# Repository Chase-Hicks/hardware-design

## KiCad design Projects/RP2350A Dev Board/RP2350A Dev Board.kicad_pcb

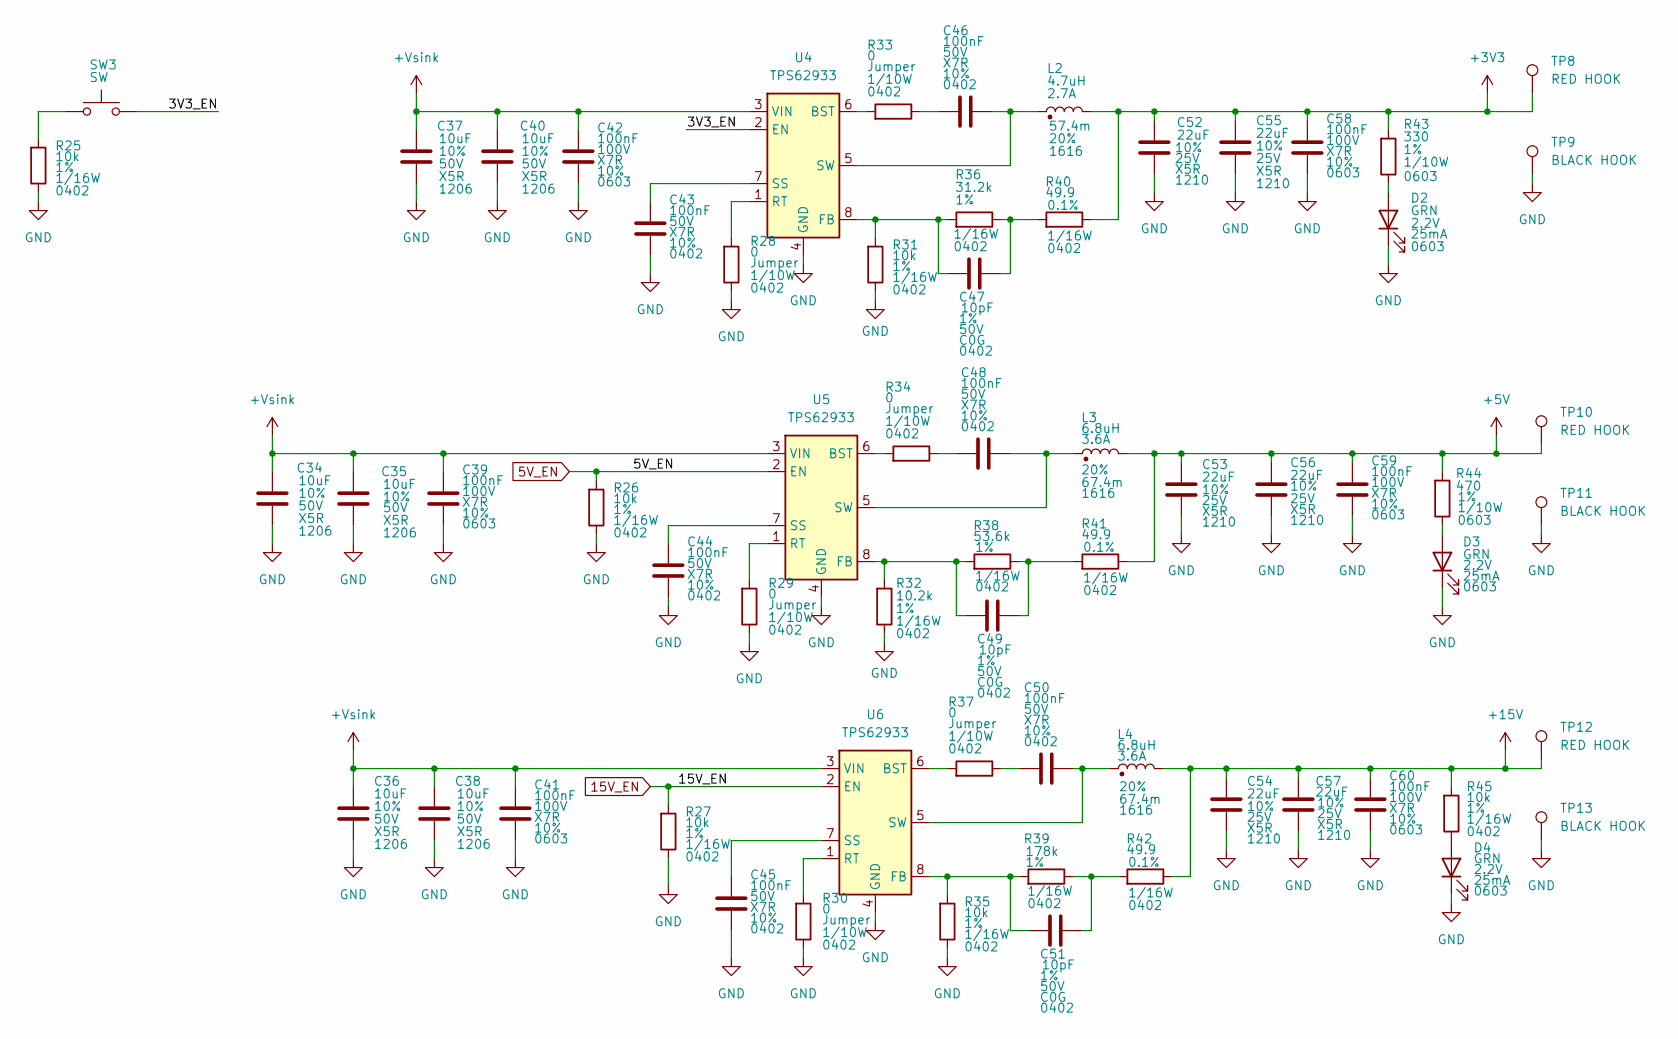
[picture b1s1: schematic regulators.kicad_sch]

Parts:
C34, C35, C36, C37, C38, C40: 10uF; C_1206_3216Metric_2; Voltage 50V; Tolerance 10%; Part Description CAP, 10uF, 25V, X5R, 10%, 1206
C39, C41, C42, C58, C59, C60: 100nF; C_0603_1608Metric_2; Voltage 100V; Tolerance 10%; Part Description CAP, 100nF, 100V, X7R, 10%, 0603
C43, C44, C45, C46, C48, C50: 100nF; C_0402_1005Metric_2; Voltage 50V; Tolerance 10%; Part Description CAP, 100nF, 50V, X7R, 10%, 0402
C47, C49, C51: 10pF; C_0402_1005Metric_2; Voltage 50V; Tolerance 1%; Part Description CAP, 10pF, 50V, C0G, 1%, 0402
C52, C53, C54, C55, C56, C57: 22uF; C_1210_3225Metric_2; Voltage 25V; Tolerance 10%; Part Description CAP, 22uF, 25V, X5R, 10%, 1210
D2, D3, D4: GRN; LED_0603_1608Metric_2; Voltage 2.2V; Part Description LED, GRN, 2.2V, 0603
L2: 4.7uH; XAL-4030-xxx; Tolerance 20%; Part Description IND, 4.7uH, 4.6A, 40.1m, 20%, 1616
L3, L4: 6.8uH; XEL-4030-xxx; Tolerance 20%; Part Description IND, 6.8uH, 3.6A, 67.4m, 20%, 1616
R25, R26, R27, R31, R35, R45: 10k; R_0402_1005Metric_2; Tolerance 1%; Part Description RESIST, 10k, 1/16W, 1%, 0402
R28, R29, R30, R33, R34, R37: 0; R_0402_1005Metric_2; Tolerance Jumper; Part Description RESIST, 0, 1/10W, 0402
R32: 10.2k; R_0402_1005Metric_2; Tolerance 1%; Part Description RESIST, 10.2k, 1/16W, 1%, 0402
R36: 31.2k; R_0402_1005Metric_2; Tolerance 1%; Part Description RESIST, 31.2k, 1/16W, 0.1%, 0402
R38: 53.6k; R_0402_1005Metric_2; Tolerance 1%; Part Description RESIST, 53.6k, 1/16W, 1%, 0402
R39: 178k; R_0402_1005Metric_2; Tolerance 1%; Part Description RESIST, 178k, 1/16W, 1%, 0402
R40, R41, R42: 49.9; R_0402_1005Metric_2; Tolerance 0.1%; Part Description RESIST, 49.9, 1/16W, 0.1%, 0403
R43: 330; R_0603_1608Metric_2; Tolerance 1%; Part Description RESIST, 330, 1/10W, 1%, 0603
R44: 470; R_0603_1608Metric_2; Tolerance 1%; Part Description RESIST, 470, 1/10W, 1%, 0603
SW3: SW; PTS815; Part Description SW, SMD, 4P
TP8, TP10, TP12: RED HOOK; KEYSTONE_519xTR; MFG PN 5190TR
TP9, TP11, TP13: BLACK HOOK; KEYSTONE_519xTR; MFG PN 5191TR
U4, U5, U6: TPS62933; SOT-583-8; Part Description IC, SMD, REG, BUCK, STEP-DOWN, 30VIN, 3A

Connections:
5V_EN: R26.1, U5.2 (EN); also elsewhere on the board
15V_EN: R27.1, U6.2 (EN); also elsewhere on the board
+3V3: C52.1, C55.1, C58.1, L2.2, R40.2, R43.1, TP8.1 (1_1); also elsewhere on the board
+5V: C53.1, C56.1, C59.1, L3.2, R41.2, R44.1, TP10.1 (1_1); also elsewhere on the board
+15V: C54.1, C57.1, C60.1, L4.2, R42.2, R45.1, TP12.1 (1_1); also elsewhere on the board
+Vsink: C34.1, C35.1, C36.1, C37.1, C38.1, C39.1, C40.1, C41.1, C42.1, U4.3 (VIN), U5.3 (VIN), U6.3 (VIN); also elsewhere on the board
/Regulators/3V3_EN: SW3.4, U4.2 (EN)
GND: C34.2, C35.2, C36.2, C37.2, C38.2, C39.2, C40.2, C41.2, C42.2, C43.2, C44.2, C45.2, C52.2, C53.2, C54.2, C55.2, C56.2, C57.2, C58.2, C59.2, C60.2, D2.1 (K), D3.1 (K), D4.1 (K), R25.2, R26.2, R27.2, R28.2, R29.2, R30.2, R31.2, R32.2, R35.2, TP9.1 (1_1), TP11.1 (1_1), TP13.1 (1_1), U4.4 (GND), U5.4 (GND), U6.4 (GND); also elsewhere on the board
unnamed: C46.1, R33.2
unnamed: C47.1, R36.2, R40.1
unnamed: C48.1, R34.2
unnamed: C49.1, R38.2, R41.1
unnamed: C50.1, R37.2
unnamed: C51.1, R39.2, R42.1
unnamed: D2.2 (A), R43.2
unnamed: D3.2 (A), R44.2
unnamed: D4.2 (A), R45.2
unnamed: R25.1, SW3.1
unnamed: R33.1, U4.6 (BST)
unnamed: C47.2, R31.1, R36.1, U4.8 (FB)
unnamed: R28.1, U4.1 (RT)
unnamed: C43.1, U4.7 (SS)
unnamed: C46.2, L2.1, U4.5 (SW)
unnamed: R34.1, U5.6 (BST)
unnamed: C49.2, R32.1, R38.1, U5.8 (FB)
unnamed: R29.1, U5.1 (RT)
unnamed: C44.1, U5.7 (SS)
unnamed: C48.2, L3.1, U5.5 (SW)
unnamed: R37.1, U6.6 (BST)
unnamed: C51.2, R35.1, R39.1, U6.8 (FB)
unnamed: R30.1, U6.1 (RT)
unnamed: C45.1, U6.7 (SS)
unnamed: C50.2, L4.1, U6.5 (SW)

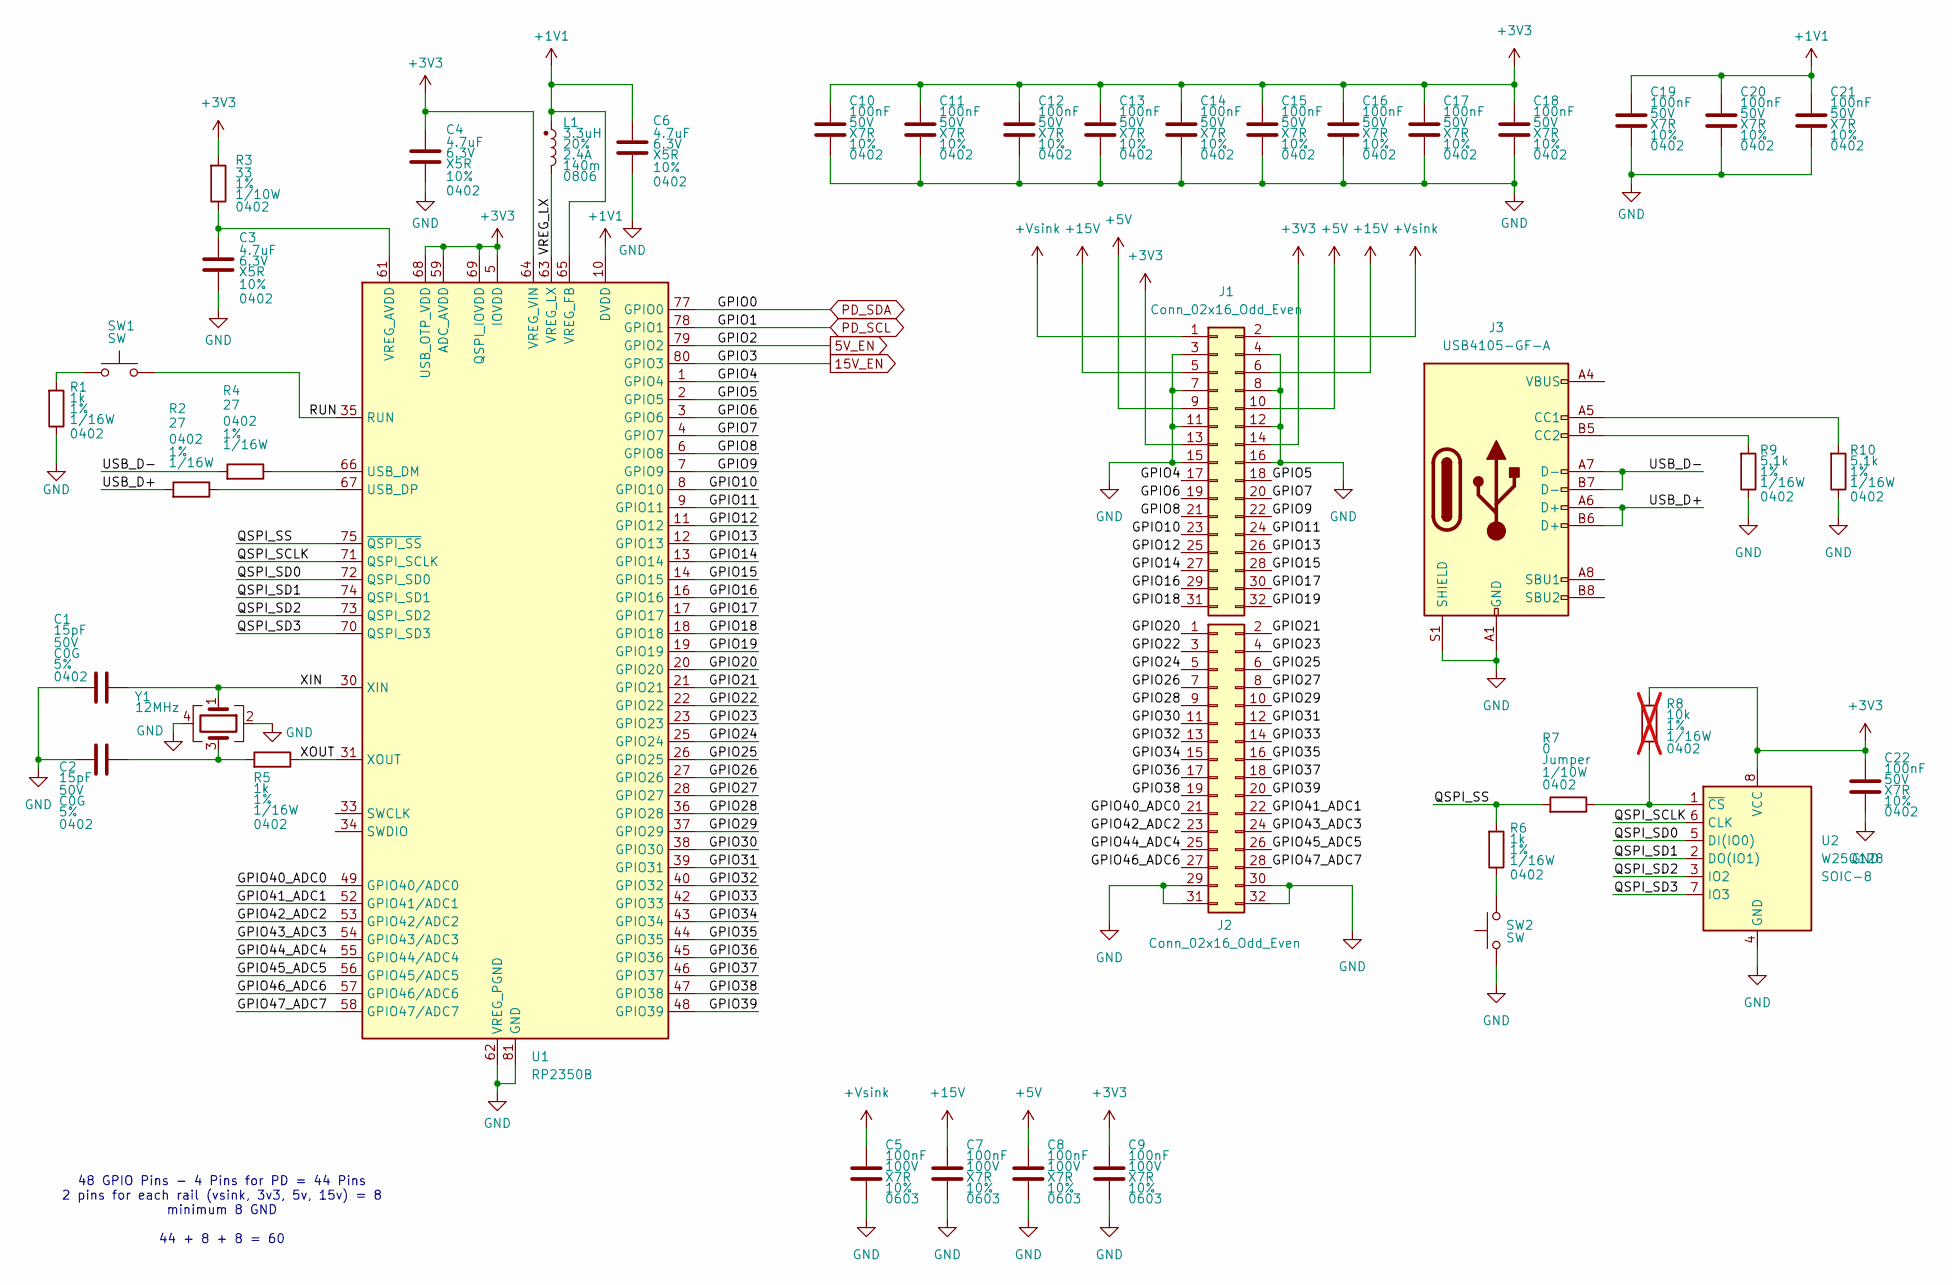
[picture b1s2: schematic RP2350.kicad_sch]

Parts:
C1, C2: 15pF; C_0402_1005Metric_2; Voltage 50V; Tolerance 5%; Part Description CAP, 15pF, 50V, C0G, 5%, 0402
C3: 4.7uF; C_0402_1005Metric_2; Voltage 6.3V; Tolerance 10%; Part Description CAP, 4.7uF, 6.3V, X5R, 10%, 0402
C4, C6: 4.7uF; C_0402_1005Metric_small_pads; Voltage 6.3V; Tolerance 10%; Part Description CAP, 4.7uF, 6.3V, X5R, 10%, 0402
C5, C7, C8, C9: 100nF; C_0603_1608Metric_2; Voltage 100V; Tolerance 10%; Part Description CAP, 100nF, 100V, X7R, 10%, 0603
C10, C11, C12, C13, C14, C15, C16, C17, C18, C19, C20, C21, C22: 100nF; C_0402_1005Metric_2; Voltage 50V; Tolerance 10%; Part Description CAP, 100nF, 50V, X7R, 10%, 0402
J1, J2: Conn_02x16_Odd_Even; PinSocket_2x16_P2.54mm_Vertical
J3: USB4105-GF-A; USB_C_Receptacle_GCT_USB4105-xx-A_16P_TopMnt_Horizontal; Part Description CONN, USB C, 2.0, 16P
L1: 3.3uH; L_pol_2016; Tolerance 20%; Part Description IND, 3.3uH, 2.4A, 140m, 20%, 0806
R1, R5, R6: 1k; R_0402_1005Metric_2; Tolerance 1%; Part Description RESIST, 1k, 1/16W, 1%, 0402
R2, R4: 27; R_0402_1005Metric_2; Tolerance 1%; Part Description RESIST, 27, 1/16W, 1%, 0402
R3: 33; R_0402_1005Metric_2; Tolerance 1%; Part Description RESIST, 33, 1/10W, 1%, 0402
R7: 0; R_0402_1005Metric_2; Tolerance Jumper; Part Description RESIST, 0, 1/10W, 0402
R8: 10k; R_0402_1005Metric_2; Tolerance 1%; Part Description RESIST, 10k, 1/16W, 1%, 0402; not fitted
R9, R10: 5.1k; R_0402_1005Metric_2; Tolerance 1%; Part Description RESIST, 5.1k, 1/16W, 1%, 0402
SW1, SW2: SW; PTS815; Part Description SW, SMD, 4P
U1: RP2350B; QFN-80-1EP_10x10mm_P0.4mm_EP3.4x3.4mm; Part Description IC, MCU, RP2350B, QFN
U2: W25Q128; SOIC-8_5.3x5.3mm_P1.27mm; Part Description IC, QSPI, 128Mb, Flash, SOIC
Y1: 12MHz; Crystal_SMD_Abracon_ABM8G-4Pin_3.2x2.5mm; Part Description CRYSTAL, 12Mhz, 30ppm, 10pF, 4-SMD

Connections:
5V_EN: U1.79 (GPIO2); also elsewhere on the board
15V_EN: U1.80 (GPIO3); also elsewhere on the board
+1V1: C6.1, C19.1, C20.1, C21.1, L1.1, U1.10 (DVDD), U1.32 (DVDD), U1.51 (DVDD), U1.65 (VREG_FB)
+3V3: C4.1, C9.1, C10.1, C11.1, C12.1, C13.1, C14.1, C15.1, C16.1, C17.1, C18.1, C22.1, J1.13, J1.14, R3.1, R8.1, U1.5 (IOVDD), U1.15 (IOVDD), U1.24 (IOVDD), U1.29 (IOVDD), U1.41 (IOVDD), U1.50 (IOVDD), U1.59 (ADC_AVDD), U1.60 (IOVDD), U1.64 (VREG_VIN), U1.68 (USB_OTP_VDD), U1.69 (QSPI_IOVDD), U1.76 (IOVDD), U2.8 (VCC); also elsewhere on the board
+5V: C8.1, J1.9, J1.10; also elsewhere on the board
+15V: C7.1, J1.5, J1.6; also elsewhere on the board
+Vsink: C5.1, J1.1, J1.2; also elsewhere on the board
/RP2350/GPIO4: J1.17, U1.1 (GPIO4)
/RP2350/GPIO5: J1.18, U1.2 (GPIO5)
/RP2350/GPIO6: J1.19, U1.3 (GPIO6)
/RP2350/GPIO7: J1.20, U1.4 (GPIO7)
/RP2350/GPIO8: J1.21, U1.6 (GPIO8)
/RP2350/GPIO9: J1.22, U1.7 (GPIO9)
/RP2350/GPIO10: J1.23, U1.8 (GPIO10)
/RP2350/GPIO11: J1.24, U1.9 (GPIO11)
/RP2350/GPIO12: J1.25, U1.11 (GPIO12)
/RP2350/GPIO13: J1.26, U1.12 (GPIO13)
/RP2350/GPIO14: J1.27, U1.13 (GPIO14)
/RP2350/GPIO15: J1.28, U1.14 (GPIO15)
/RP2350/GPIO16: J1.29, U1.16 (GPIO16)
/RP2350/GPIO17: J1.30, U1.17 (GPIO17)
/RP2350/GPIO18: J1.31, U1.18 (GPIO18)
/RP2350/GPIO19: J1.32, U1.19 (GPIO19)
/RP2350/GPIO20: J2.1, U1.20 (GPIO20)
/RP2350/GPIO21: J2.2, U1.21 (GPIO21)
/RP2350/GPIO22: J2.3, U1.22 (GPIO22)
/RP2350/GPIO23: J2.4, U1.23 (GPIO23)
/RP2350/GPIO24: J2.5, U1.25 (GPIO24)
/RP2350/GPIO25: J2.6, U1.26 (GPIO25)
/RP2350/GPIO26: J2.7, U1.27 (GPIO26)
/RP2350/GPIO27: J2.8, U1.28 (GPIO27)
/RP2350/GPIO28: J2.9, U1.36 (GPIO28)
/RP2350/GPIO29: J2.10, U1.37 (GPIO29)
/RP2350/GPIO30: J2.11, U1.38 (GPIO30)
/RP2350/GPIO31: J2.12, U1.39 (GPIO31)
/RP2350/GPIO32: J2.13, U1.40 (GPIO32)
/RP2350/GPIO33: J2.14, U1.42 (GPIO33)
/RP2350/GPIO34: J2.15, U1.43 (GPIO34)
/RP2350/GPIO35: J2.16, U1.44 (GPIO35)
/RP2350/GPIO36: J2.17, U1.45 (GPIO36)
/RP2350/GPIO37: J2.18, U1.46 (GPIO37)
/RP2350/GPIO38: J2.19, U1.47 (GPIO38)
/RP2350/GPIO39: J2.20, U1.48 (GPIO39)
/RP2350/GPIO40_ADC0: J2.21, U1.49 (GPIO40/ADC0)
/RP2350/GPIO41_ADC1: J2.22, U1.52 (GPIO41/ADC1)
/RP2350/GPIO42_ADC2: J2.23, U1.53 (GPIO42/ADC2)
/RP2350/GPIO43_ADC3: J2.24, U1.54 (GPIO43/ADC3)
/RP2350/GPIO44_ADC4: J2.25, U1.55 (GPIO44/ADC4)
/RP2350/GPIO45_ADC5: J2.26, U1.56 (GPIO45/ADC5)
/RP2350/GPIO46_ADC6: J2.27, U1.57 (GPIO46/ADC6)
/RP2350/GPIO47_ADC7: J2.28, U1.58 (GPIO47/ADC7)
/RP2350/QSPI_SCLK: U1.71 (QSPI_SCLK), U2.6 (CLK)
/RP2350/QSPI_SD0: U1.72 (QSPI_SD0), U2.5 (DI(IO0))
/RP2350/QSPI_SD1: U1.74 (QSPI_SD1), U2.2 (DO(IO1))
/RP2350/QSPI_SD2: U1.73 (QSPI_SD2), U2.3 (IO2)
/RP2350/QSPI_SD3: U1.70 (QSPI_SD3), U2.7 (IO3)
/RP2350/QSPI_SS: R6.1, R7.1, U1.75 (~QSPI_SS)
/RP2350/RUN: SW1.4, U1.35 (RUN)
/RP2350/USB_D+: J3.A6 (D+), J3.B6 (D+), R2.1
/RP2350/USB_D-: J3.A7 (D-), J3.B7 (D-), R4.1
/RP2350/VREG_LX: L1.2, U1.63 (VREG_LX)
/RP2350/XIN: C1.2, U1.30 (XIN), Y1.1
/RP2350/XOUT: R5.2, U1.31 (XOUT)
GND: C1.1, C2.1, C3.2, C4.2, C5.2, C6.2, C7.2, C8.2, C9.2, C10.2, C11.2, C12.2, C13.2, C14.2, C15.2, C16.2, C17.2, C18.2, C19.2, C20.2, C21.2, C22.2, J1.3, J1.4, J1.7, J1.8, J1.11, J1.12, J1.15, J1.16, J2.29, J2.30, J2.31, J2.32, J3.A1 (GND), J3.A12 (GND), J3.B1 (GND), J3.B12 (GND), J3.S1 (SHIELD), R1.2, R9.2, R10.2, SW2.1, U1.62 (VREG_PGND), U1.81 (GND), U2.4 (GND), Y1.2, Y1.4; also elsewhere on the board
unnamed: C2.2, R5.1, Y1.3
unnamed: J3.A5 (CC1), R10.1
unnamed: J3.B5 (CC2), R9.1
unnamed: J3.A4 (VBUS), J3.A9 (VBUS), J3.B4 (VBUS), J3.B9 (VBUS)
unnamed: R1.1, SW1.1
unnamed: R6.2, SW2.4
unnamed: R4.2, U1.66 (USB_DM)
unnamed: R2.2, U1.67 (USB_DP)
unnamed: C3.1, R3.2, U1.61 (VREG_AVDD)
unnamed: R7.2, R8.2, U2.1 (~CS)
PD_SCL: U1.78 (GPIO1); also elsewhere on the board
PD_SDA: U1.77 (GPIO0); also elsewhere on the board

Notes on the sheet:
48 GPIO Pins - 4 Pins for PD = 44 Pins 2 pins for each rail (vsink, 3v3, 5v, 15v) = 8 minimum 8 GND 44 + 8 + 8 = 60

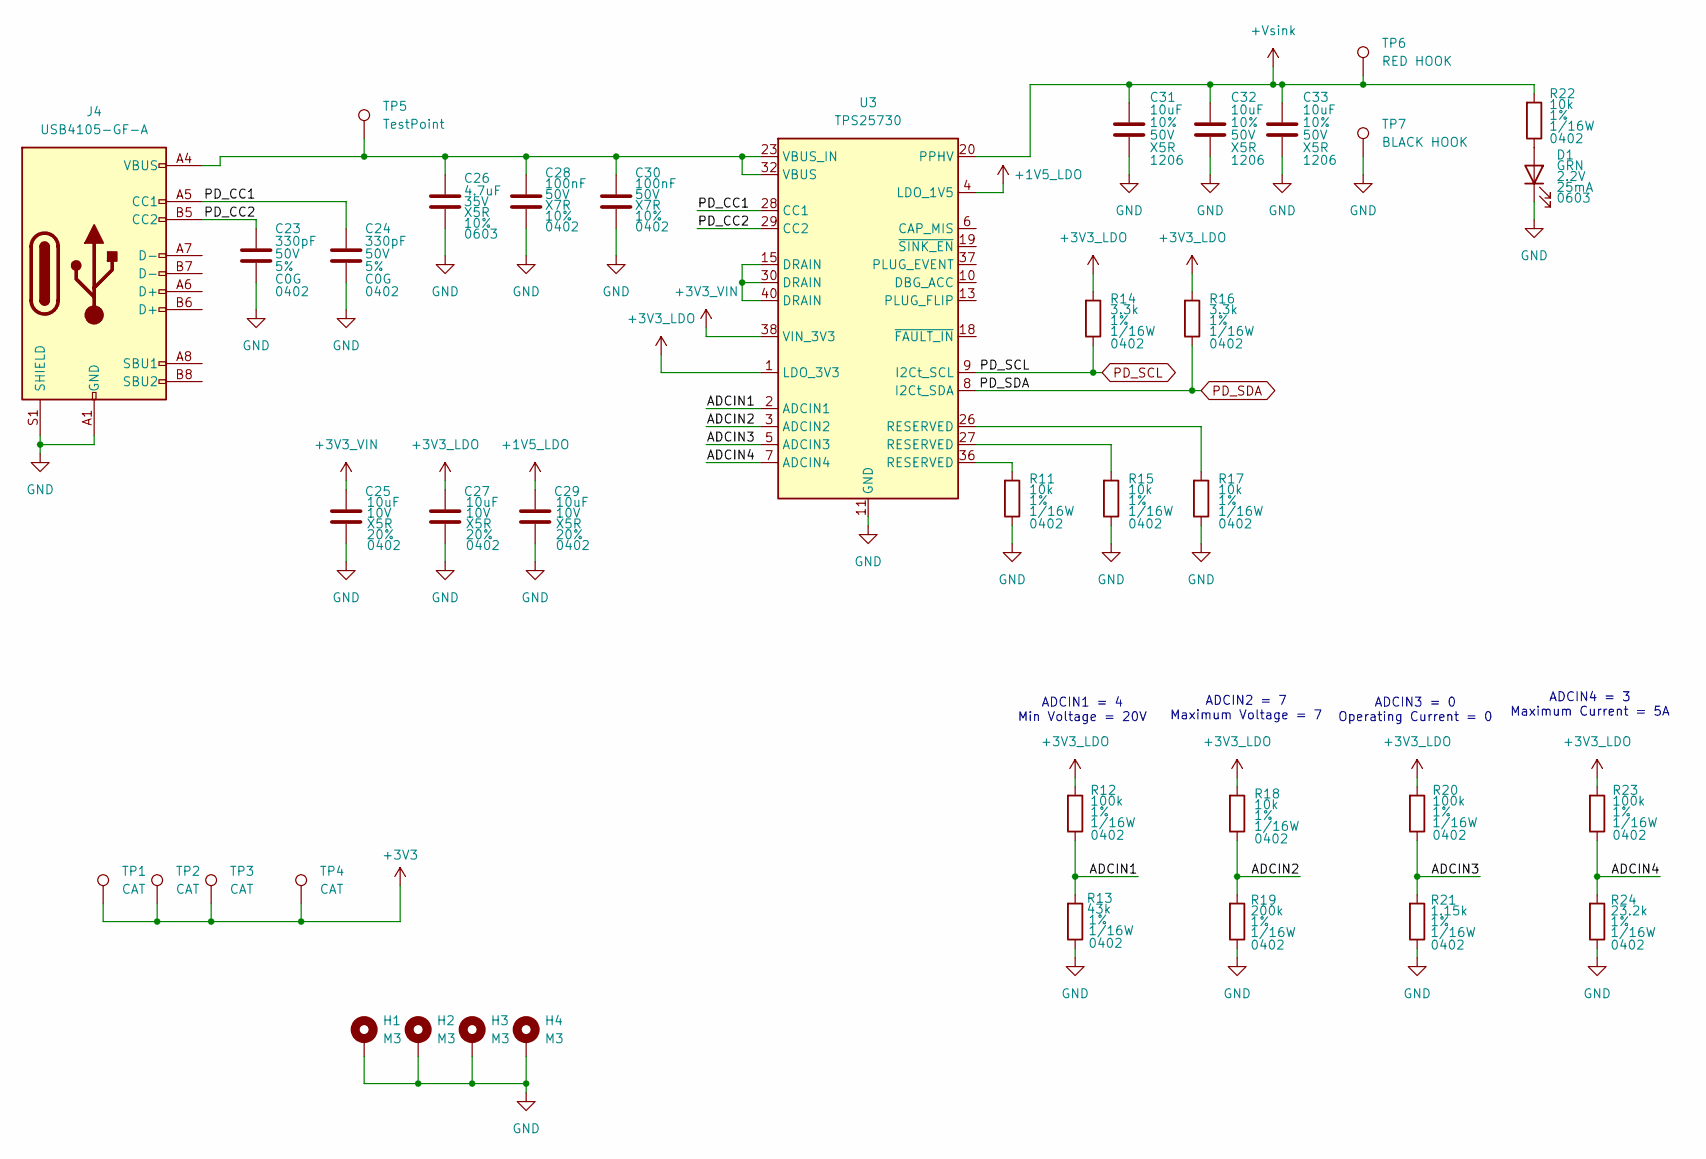
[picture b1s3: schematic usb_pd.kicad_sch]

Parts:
C23, C24: 330pF; C_0402_1005Metric_2; Voltage 50V; Tolerance 5%; Part Description CAP, 330pF, 50V, C0G, 5%, 0402
C25, C27, C29: 10uF; C_0402_1005Metric_2; Voltage 10V; Tolerance 20%; Part Description CAP, 10uF, 10V, X5R, 20%, 0402
C26: 4.7uF; C_0603_1608Metric_2; Voltage 35V; Tolerance 10%; Part Description CAP, 4.7uF, 35V, X5R, 10%, 0603
C28, C30: 100nF; C_0402_1005Metric_2; Voltage 50V; Tolerance 10%; Part Description CAP, 100nF, 50V, X7R, 10%, 0402
C31, C32, C33: 10uF; C_1206_3216Metric_2; Voltage 50V; Tolerance 10%; Part Description CAP, 10uF, 25V, X5R, 10%, 1206
D1: GRN; LED_0603_1608Metric_2; Voltage 2.2V; Part Description LED, GRN, 2.2V, 0603
H1, H2, H3, H4: M3; MountingHole_3.2mm_M3_Pad_Via; MFG PN N/A
J4: USB4105-GF-A; USB_C_Receptacle_GCT_USB4105-xx-A_16P_TopMnt_Horizontal; Part Description CONN, USB C, 2.0, 16P
R11, R15, R17, R18, R22: 10k; R_0402_1005Metric_2; Tolerance 1%; Part Description RESIST, 10k, 1/16W, 1%, 0402
R12, R20, R23: 100k; R_0402_1005Metric_2; Tolerance 1%; Part Description RESIST, 100k, 1/16W, 1%, 0402
R13: 43k; R_0402_1005Metric_2; Tolerance 1%; Part Description RESIST, 43k, 1/16W, 1%, 0402
R14, R16: 3.3k; R_0402_1005Metric_2; Tolerance 1%; Part Description RESIST, 3.3k, 1/16W, 1%, 0402
R19: 200k; R_0402_1005Metric_2; Tolerance 1%; Part Description RESIST, 200k, 1/16W, 1%, 0402
R21: 1.15k; R_0402_1005Metric_2; Tolerance 1%; Part Description RESIST, 1.15k, 1/16W, 1%, 0402
R24: 23.2k; R_0402_1005Metric_2; Tolerance 1%; Part Description RESIST, 23.2k, 1/16W, 1%, 0402
TP1: CAT; Cat_4
TP2: CAT; Cat_3
TP3: CAT; Cat_2
TP4: CAT; Cat
TP5: TestPoint; TestPoint_Pad_D1.0mm
TP6: RED HOOK; KEYSTONE_519xTR; MFG PN 5190TR
TP7: BLACK HOOK; KEYSTONE_519xTR; MFG PN 5191TR
U3: TPS25730; Texas_REF0038A_WQFN-38-2EP_6x4mm_P0.4; Part Description IC, USB PD, FET, WQFN-38

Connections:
+1V5_LDO: C29.1, U3.4 (LDO_1V5)
+3V3_LDO: C27.1, R12.1, R14.1, R16.1, R18.1, R20.1, R23.1, U3.1 (LDO_3V3)
+3V3_VIN: C25.1, U3.38 (VIN_3V3)
+Vsink: C31.1, C32.1, C33.1, R22.1, TP6.1 (1_1), U3.20 (PPHV); also elsewhere on the board
/USB PD/ADCIN1: R12.2, R13.1, U3.2 (ADCIN1)
/USB PD/ADCIN2: R18.2, R19.1, U3.3 (ADCIN2)
/USB PD/ADCIN3: R20.2, R21.1, U3.5 (ADCIN3)
/USB PD/ADCIN4: R23.2, R24.1, U3.7 (ADCIN4)
/USB PD/PD_CC1: C24.1, J4.A5 (CC1), U3.28 (CC1)
/USB PD/PD_CC2: C23.1, J4.B5 (CC2), U3.29 (CC2)
GND: C23.2, C24.2, C25.2, C26.2, C27.2, C28.2, C29.2, C30.2, C31.2, C32.2, C33.2, D1.1 (K), H1.1 (1_1), H2.1 (1_1), H3.1 (1_1), H4.1 (1_1), J4.A1 (GND), J4.A12 (GND), J4.B1 (GND), J4.B12 (GND), J4.S1 (SHIELD), R11.2, R13.2, R15.2, R17.2, R19.2, R21.2, R24.2, TP7.1 (1_1), U3.11 (GND), U3.12 (GND), U3.14 (GND), U3.16 (GND), U3.17 (GND), U3.31 (GND), U3.34 (GND), U3.39 (GND); also elsewhere on the board
unnamed: D1.2 (A), R22.2
unnamed: R11.1, U3.36 (RESERVED)
unnamed: R15.1, U3.27 (RESERVED)
unnamed: R17.1, U3.26 (RESERVED)
unnamed: U3.15 (DRAIN), U3.30 (DRAIN), U3.40 (DRAIN)
unnamed: C26.1, C28.1, C30.1, J4.A4 (VBUS), J4.A9 (VBUS), J4.B4 (VBUS), J4.B9 (VBUS), TP5.1 (1_1), U3.23 (VBUS_IN), U3.32 (VBUS)
PD_SCL: R14.2, U3.9 (I2Ct_SCL); also elsewhere on the board
PD_SDA: R16.2, U3.8 (I2Ct_SDA); also elsewhere on the board

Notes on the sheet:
ADCIN4 = 3 Maximum Current = 5A
ADCIN2 = 7 Maximum Voltage = 7
ADCIN3 = 0 Operating Current = 0
ADCIN1 = 4 Min Voltage = 20V

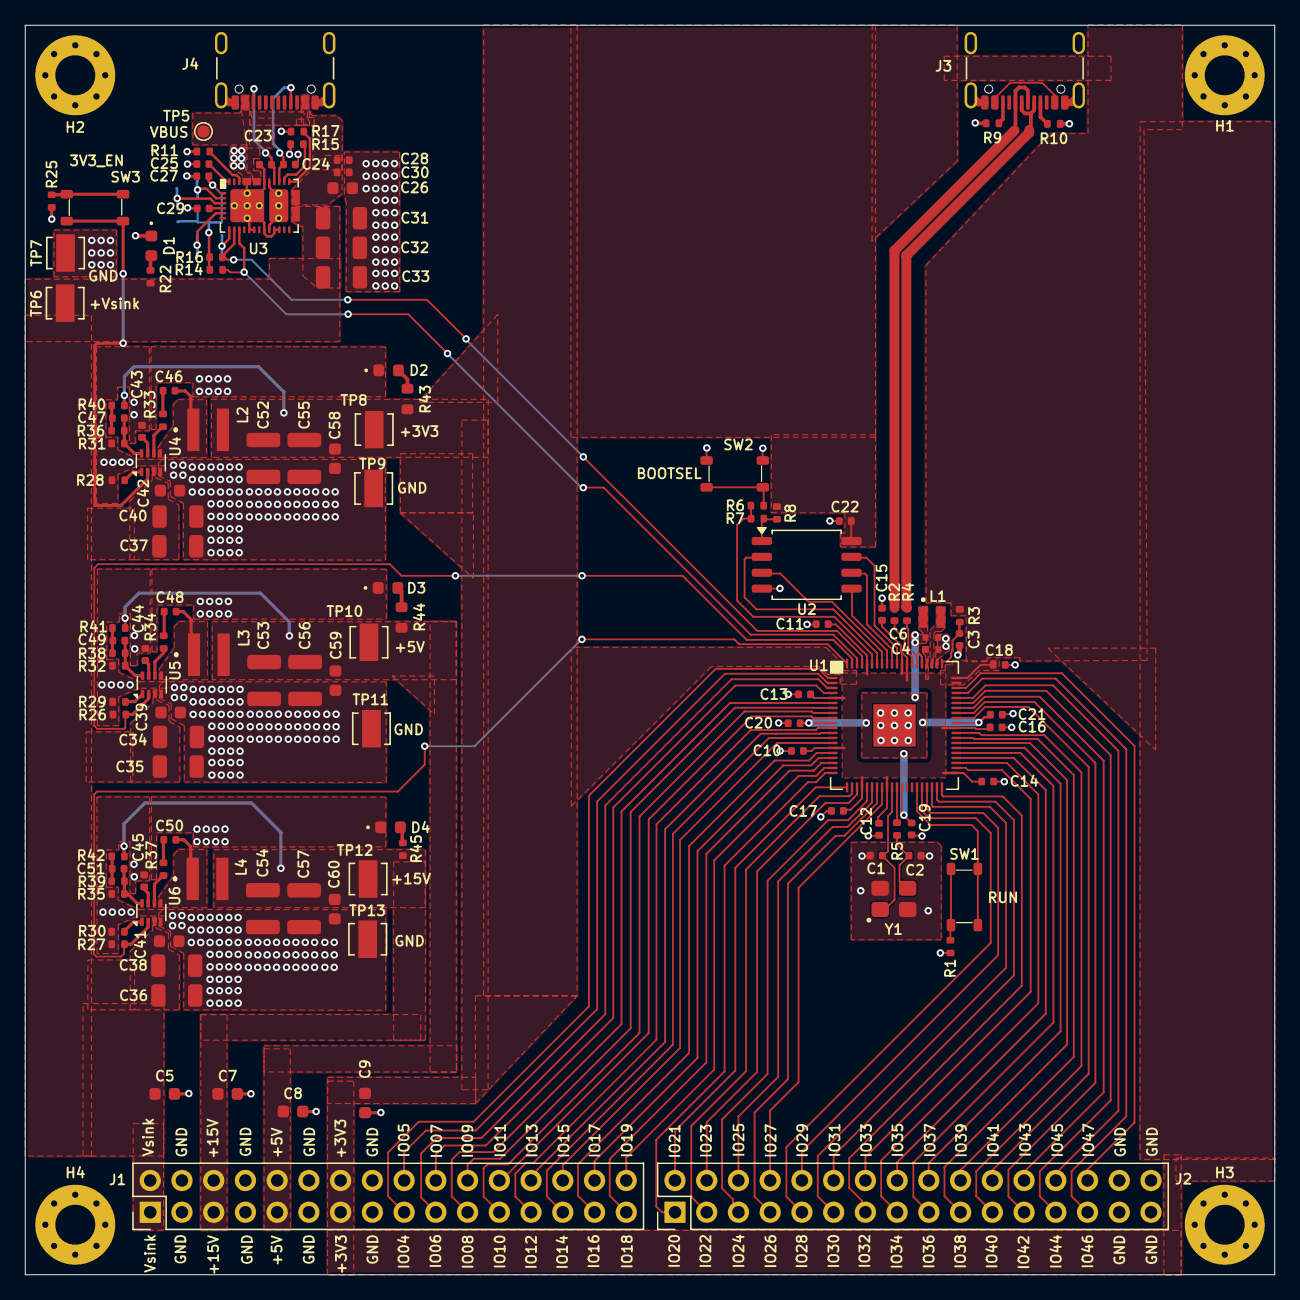
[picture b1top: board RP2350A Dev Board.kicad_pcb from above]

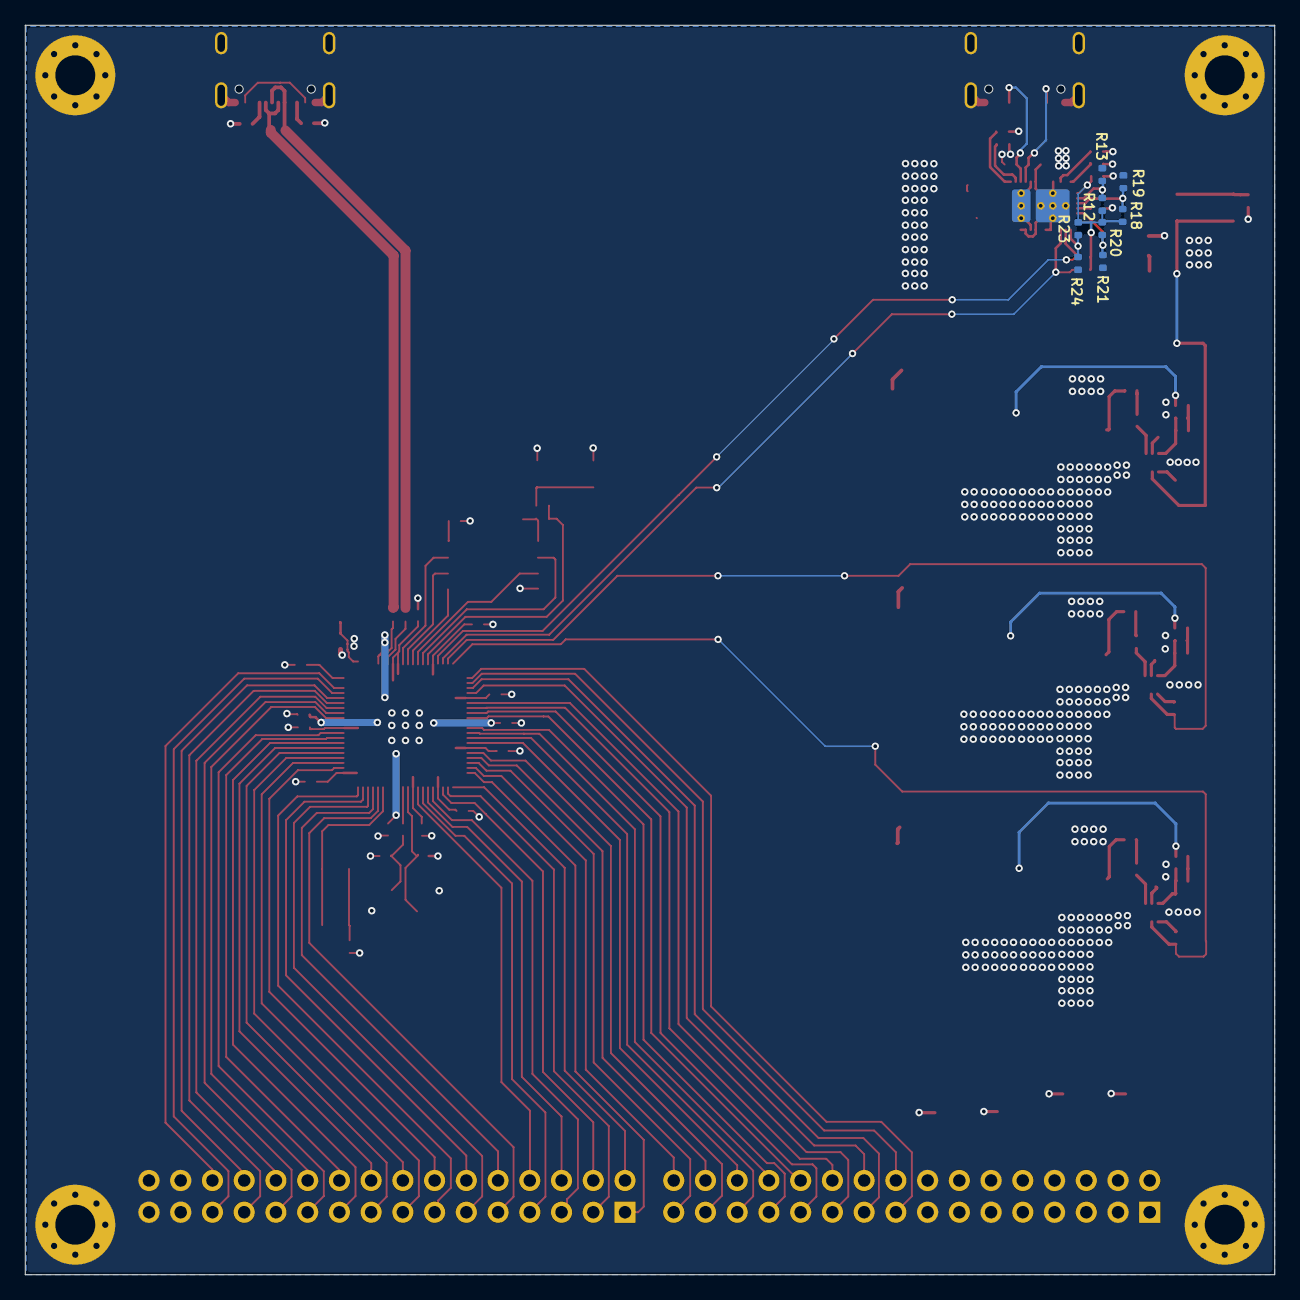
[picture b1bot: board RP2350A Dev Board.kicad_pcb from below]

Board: 2 copper layers, 100.0 x 100.0 mm, 144 parts (8 on the bottom side), 117 nets.
